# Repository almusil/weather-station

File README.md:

# weather-station

## Node
### Bulding build container
Build node building container, under project root directory: 
```
docker build --rm \
 -t weather-station/node-build-image \
 -f ./docker/Dockerfile.node \
 .
 ```

New container is needed in case you want to update libopencm3 to the latest
or bump ARM GCC version.

### Running build
Build node source, under project root directory: 
```
./scripts/run-build-node.sh
```

Open the container shell without executing the build run: 
```
./scripts/run-build-node.sh --shell
```

## Schematic and board
Schematic and board design are under HW directory

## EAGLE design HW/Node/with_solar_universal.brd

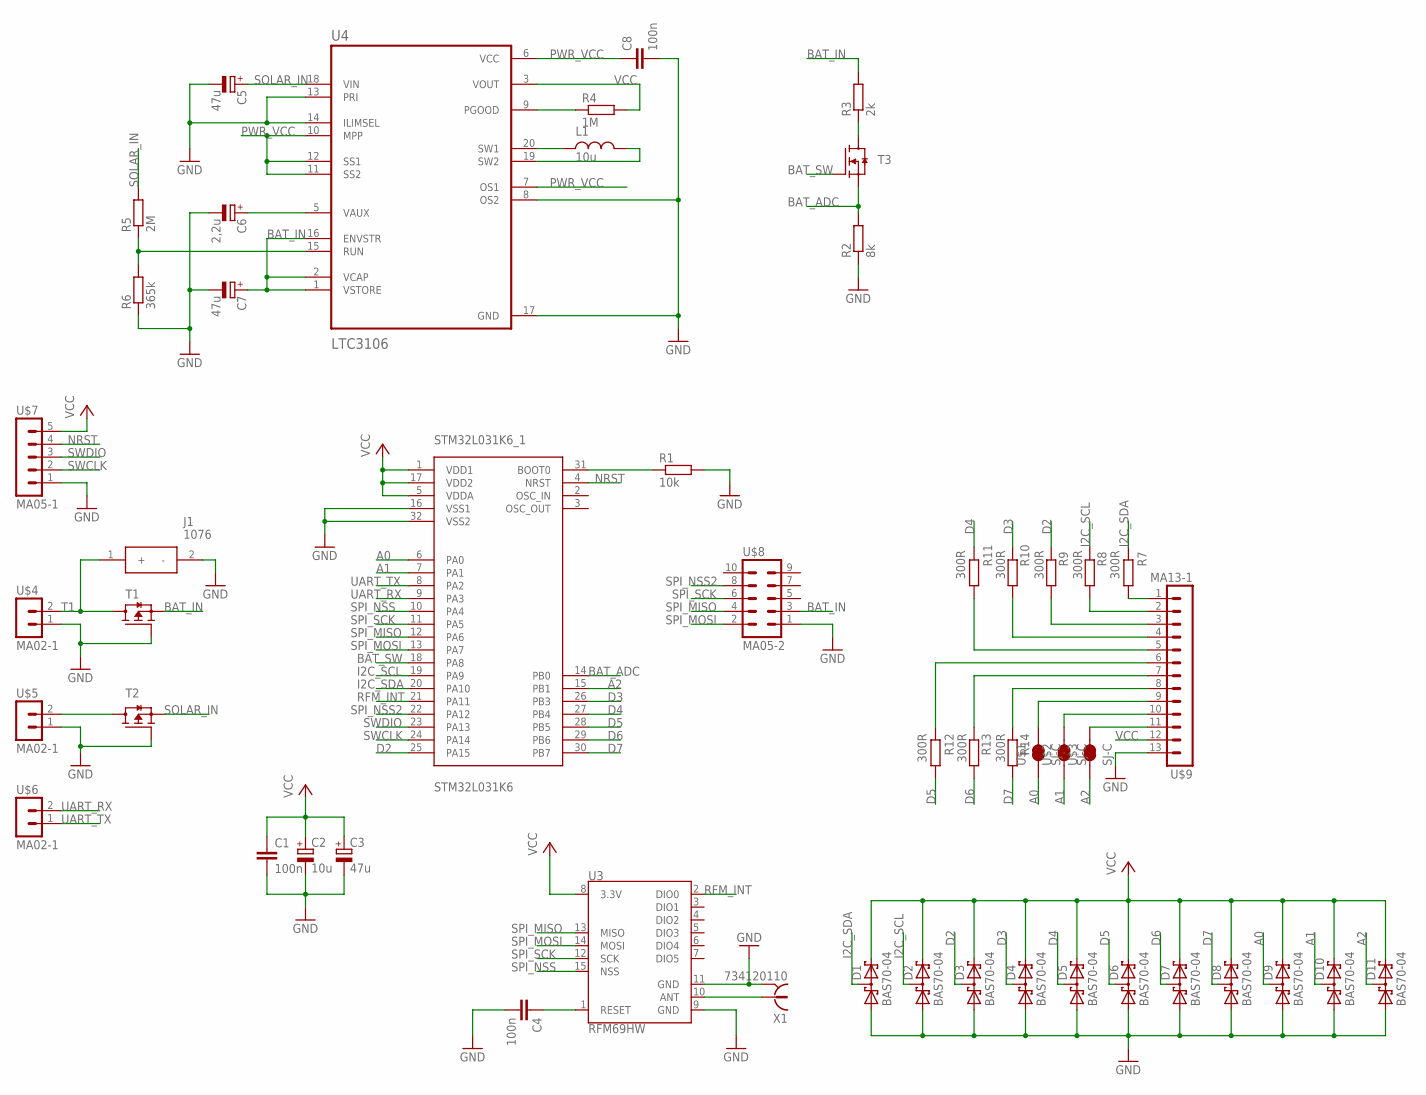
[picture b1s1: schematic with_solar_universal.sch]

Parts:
C1, C4, C8: 100n; C1206
C2: 10u; UD-4X5,8_NICHICON
C3, C5, C7: 47u; UD-4X5,8_NICHICON
C6: 2,2u; UD-4X5,8_NICHICON
D1, D2, D3, D4, D5, D6, D7, D8, D9, D10, D11: BAS70-04; SOT23
J1: 1076
L1: 10u; R1210
R1: 10k; R0805
R2: 8k; R0805
R3: 2k; R0805
R4: 1M; R0805
R5: 2M; R0805
R6: 365k; R0805
R7, R8, R9, R10, R11, R12, R13, R14: 300R; R0805
STM32L031K6_1: STM32L031K6; LQFP32-7X7
T1, T2: RTQ035P02HZG; SOT457R_PHILIPS
T3: RQ6E050AJTCR; SOT457R_PHILIPS
U3: RFM69HW; RFM69W-XXXS2
U4: LTC3106
U$1, U$2, U$3: SJ-C; R0805
U$4, U$5, U$6: MA02-1
U$7: MA05-1
U$8: MA05-2
U$9: MA13-1
X1: 734120110

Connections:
A0: D9.3 (K1A2), STM32L031K6_1.6 (PA0), U$1.1
A1: D10.3 (K1A2), STM32L031K6_1.7 (PA1), U$2.1
A2: D11.3 (K1A2), STM32L031K6_1.15 (PB1), U$3.1
BAT_ADC: R2.2, STM32L031K6_1.14 (PB0), T3.4 (S)
BAT_IN: C7.+, R3.2, T1.4 (S), U4.1 (VSTORE), U4.2 (VCAP), U4.16 (ENVSTR), U$8.3
BAT_SW: STM32L031K6_1.18 (PA8), T3.3 (G)
D2: D3.3 (K1A2), R9.2, STM32L031K6_1.25 (PA15)
D3: D4.3 (K1A2), R10.2, STM32L031K6_1.26 (PB3)
D4: D5.3 (K1A2), R11.2, STM32L031K6_1.27 (PB4)
D5: D6.3 (K1A2), R12.2, STM32L031K6_1.28 (PB5)
D6: D7.3 (K1A2), R13.2, STM32L031K6_1.29 (PB6)
D7: D8.3 (K1A2), R14.2, STM32L031K6_1.30 (PB7)
GND: C1.2, C2.-, C3.-, C4.2, C5.-, C6.-, C7.-, C8.2, D1.1 (A1), D2.1 (A1), D3.1 (A1), D4.1 (A1), D5.1 (A1), D6.1 (A1), D7.1 (A1), D8.1 (A1), D9.1 (A1), D10.1 (A1), D11.1 (A1), J1.2 (-), R1.2, R2.1, R6.1, STM32L031K6_1.16 (VSS1), STM32L031K6_1.32 (VSS2), T1.3 (G), T2.3 (G), U3.9 (GND), U3.11 (GND), U4.8 (OS2), U4.13 (PRI), U4.14 (ILIMSEL), U4.17 (GND), U$4.1 (2), U$5.1 (2), U$7.1, U$8.1, U$9.13, X1.S@1 (2), X1.S@2 (2), X1.S@3 (2)
I2C_SCL: D2.3 (K1A2), R8.2, STM32L031K6_1.19 (PA9)
I2C_SDA: D1.3 (K1A2), R7.2, STM32L031K6_1.20 (PA10)
unnamed: R1.1, STM32L031K6_1.31 (BOOT0)
unnamed: U3.10 (ANT), X1.1
unnamed: L1.1, U4.20 (SW1)
unnamed: L1.2, U4.19 (SW2)
unnamed: C6.+, U4.5 (VAUX)
unnamed: R4.1, U4.9 (PGOOD)
unnamed: R5.1, R6.2, U4.15 (RUN)
unnamed: R7.1, U$9.1
unnamed: R8.1, U$9.2
unnamed: C4.1, U3.1 (RESET)
unnamed: R9.1, U$9.3
unnamed: R10.1, U$9.4
unnamed: R11.1, U$9.5
unnamed: R12.1, U$9.6
unnamed: R13.1, U$9.7
unnamed: R14.1, U$9.8
unnamed: U$1.2, U$9.9
unnamed: U$2.2, U$9.10
unnamed: R3.1, T3.1 (D), T3.2 (D), T3.5 (D), T3.6 (D)
unnamed: U$3.2, U$9.11
NRST: STM32L031K6_1.4 (NRST), U$7.4
PWR_VCC: C8.1, U4.6 (VCC), U4.7 (OS1), U4.10 (MPP), U4.11 (SS2), U4.12 (SS1)
RFM_INT: STM32L031K6_1.21 (PA11), U3.2 (DIO0)
SOLAR_IN: C5.+, R5.2, T2.4 (S), U4.18 (VIN)
SPI_MISO: STM32L031K6_1.12 (PA6), U3.13 (MISO), U$8.4
SPI_MOSI: STM32L031K6_1.13 (PA7), U3.14 (MOSI), U$8.2
SPI_NSS: STM32L031K6_1.10 (PA4), U3.15 (NSS)
SPI_NSS2: STM32L031K6_1.22 (PA12), U$8.8
SPI_SCK: STM32L031K6_1.11 (PA5), U3.12 (SCK), U$8.6
SWCLK: STM32L031K6_1.24 (PA14), U$7.2
SWDIO: STM32L031K6_1.23 (PA13), U$7.3
T1: J1.1 (+), T1.1 (D), T1.2 (D), T1.5 (D), T1.6 (D), U$4.2 (3)
T2: T2.1 (D), T2.2 (D), T2.5 (D), T2.6 (D), U$5.2 (3)
UART_RX: STM32L031K6_1.9 (PA3), U$6.2 (3)
UART_TX: STM32L031K6_1.8 (PA2), U$6.1 (2)
VCC: C1.1, C2.+, C3.+, D1.2 (K2), D2.2 (K2), D3.2 (K2), D4.2 (K2), D5.2 (K2), D6.2 (K2), D7.2 (K2), D8.2 (K2), D9.2 (K2), D10.2 (K2), D11.2 (K2), R4.2, STM32L031K6_1.1 (VDD1), STM32L031K6_1.5 (VDDA), STM32L031K6_1.17 (VDD2), U3.8 (3.3V), U4.3 (VOUT), U$7.5, U$9.12

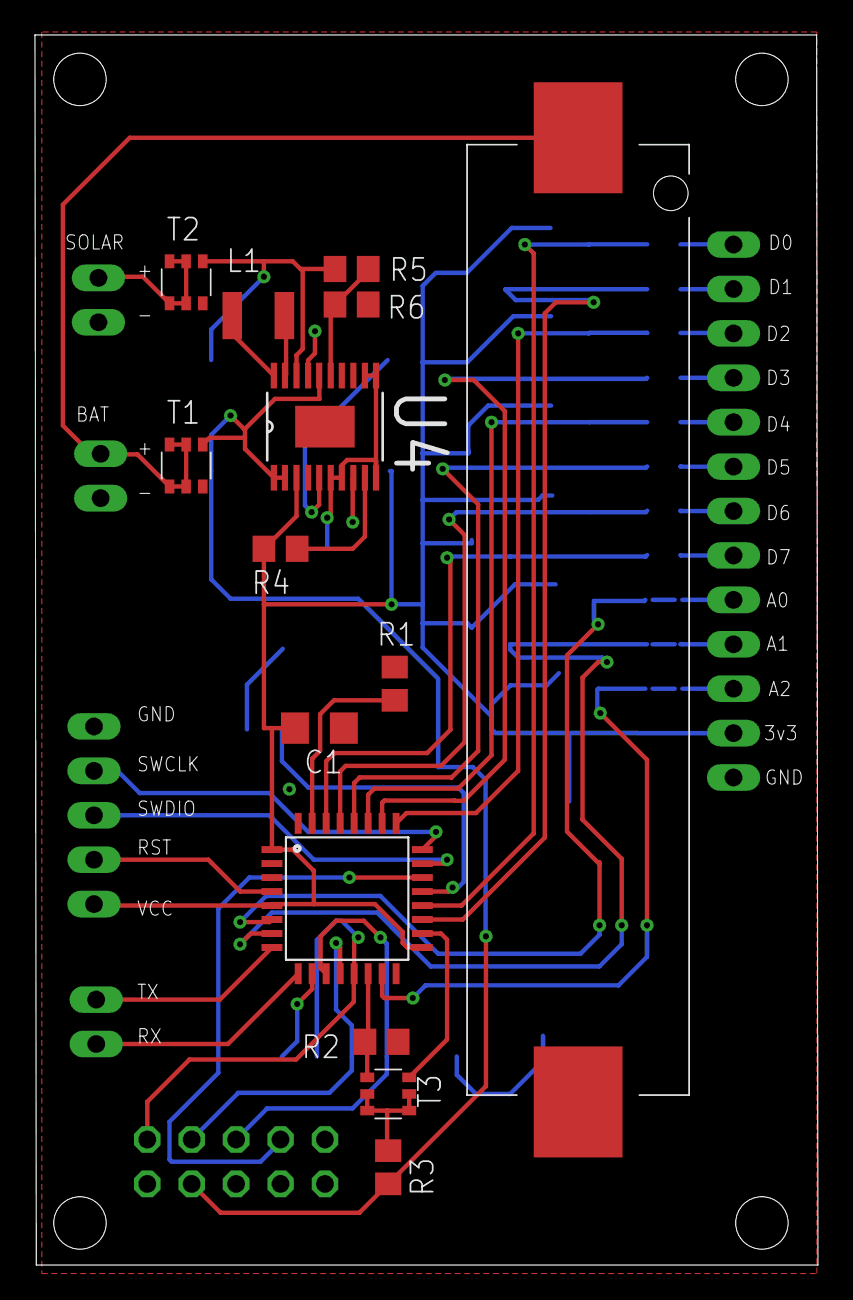
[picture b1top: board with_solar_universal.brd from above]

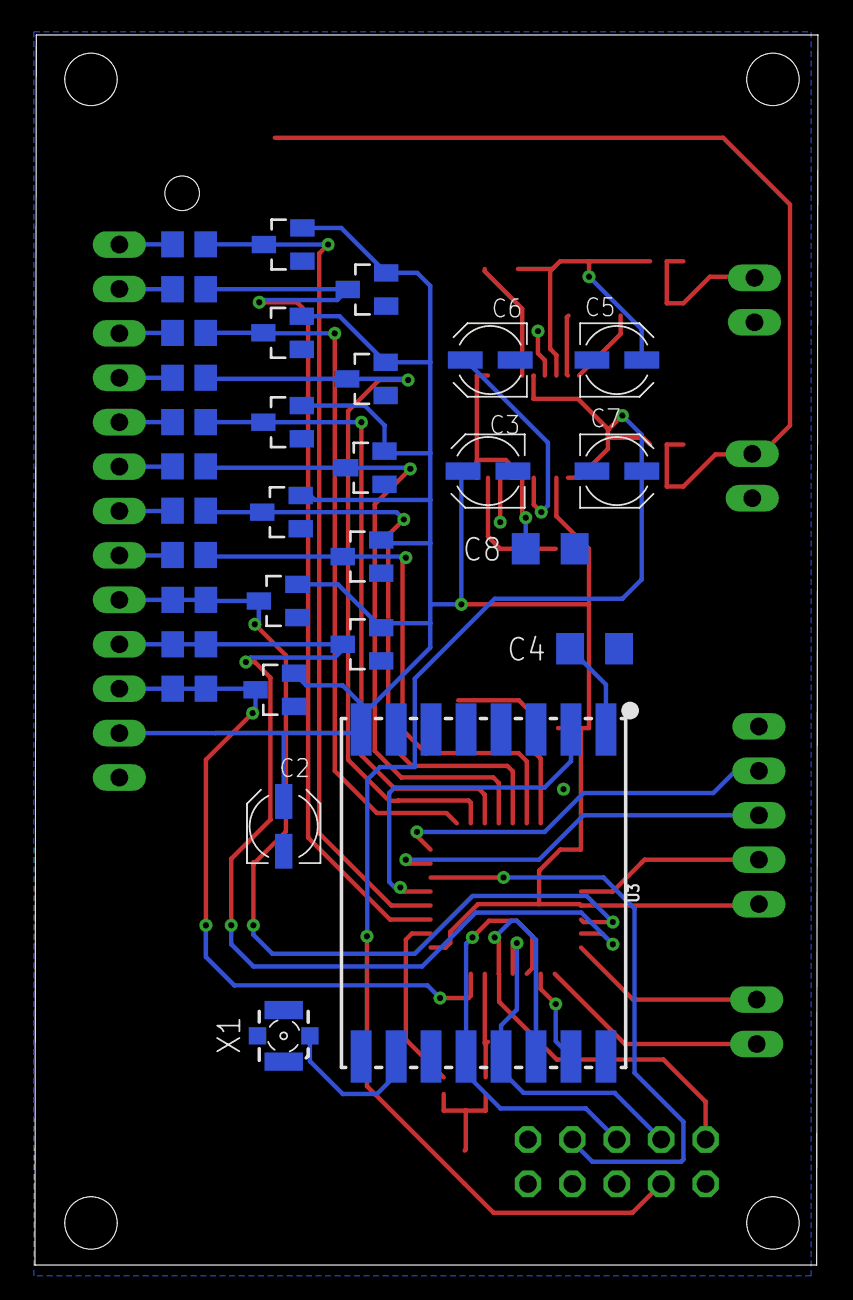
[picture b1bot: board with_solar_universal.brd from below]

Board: 2 copper layers, 44.8 x 70.3 mm, 51 parts (31 on the bottom side), 51 nets.

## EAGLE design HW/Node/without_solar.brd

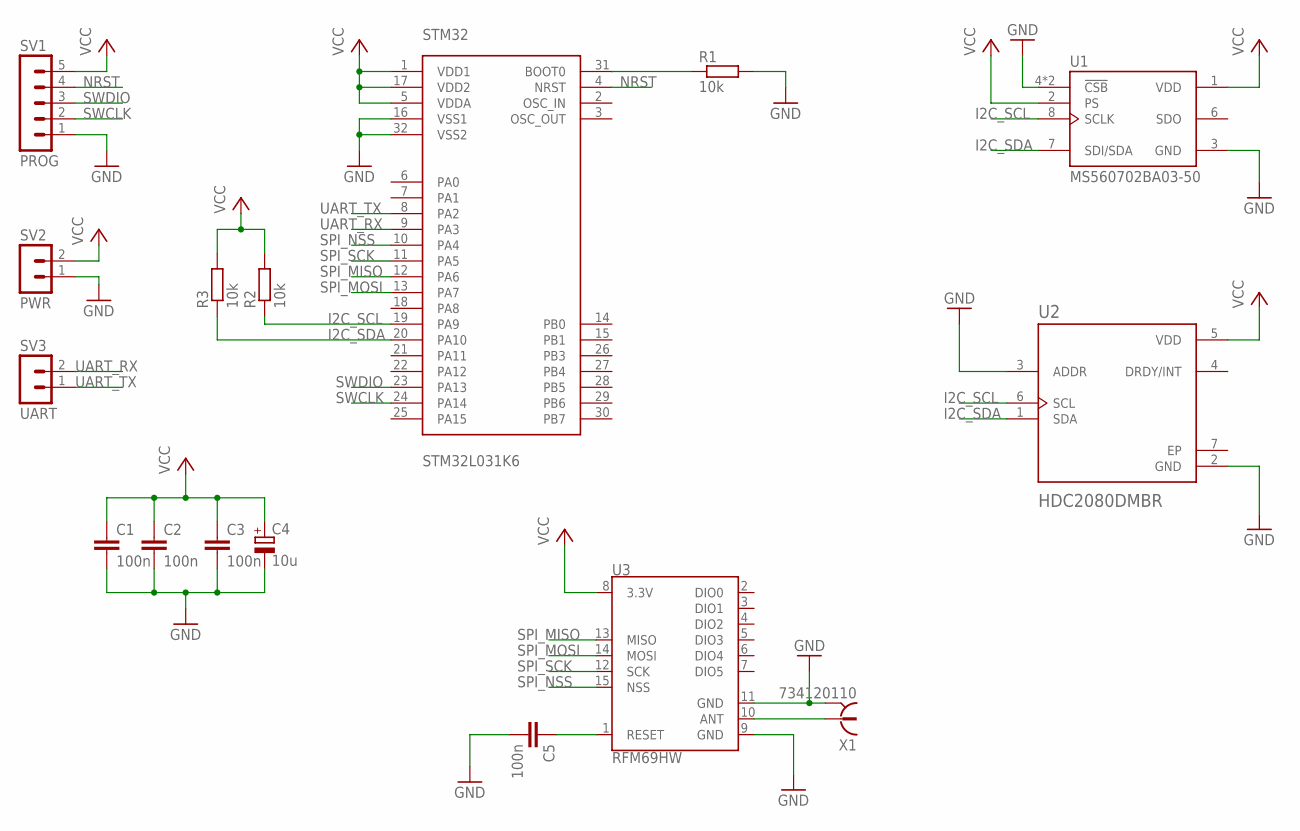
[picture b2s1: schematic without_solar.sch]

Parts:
C1, C2, C3, C5: 100n; C1206
C4: 10u; UD-4X5,8_NICHICON
R1, R2, R3: 10k; R0805
STM32: STM32L031K6; LQFP32-7X7
SV1: PROG; MA05-1
SV2: PWR; MA02-1
SV3: UART; MA02-1
U1: MS560702BA03-50; SON125P300X500X100-8N
U2: HDC2080DMBR; SON100P300X300X80-7N
U3: RFM69HW; RFM69W-XXXS2
X1: 734120110

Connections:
GND: C1.2, C2.2, C3.2, C4.-, C5.2, R1.2, STM32.16 (VSS1), STM32.32 (VSS2), SV1.1, SV2.1 (2), U1.3 (GND), U1.4 (!CSB), U1.5 (!CSB), U2.2 (GND), U2.3 (ADDR), U3.9 (GND), U3.11 (GND), X1.S@1 (2), X1.S@2 (2), X1.S@3 (2)
I2C_SCL: R2.1, STM32.19 (PA9), U1.8 (SCLK), U2.6 (SCL)
I2C_SDA: R3.1, STM32.20 (PA10), U1.7 (SDI/SDA), U2.1 (SDA)
unnamed: R1.1, STM32.31 (BOOT0)
unnamed: U3.10 (ANT), X1.1
unnamed: C5.1, U3.1 (RESET)
NRST: STM32.4 (NRST), SV1.4
RFM_INT: STM32.7 (PA1), U3.2 (DIO0)
SPI_MISO: STM32.12 (PA6), U3.13 (MISO)
SPI_MOSI: STM32.13 (PA7), U3.14 (MOSI)
SPI_NSS: STM32.10 (PA4), U3.15 (NSS)
SPI_SCK: STM32.11 (PA5), U3.12 (SCK)
SWCLK: STM32.24 (PA14), SV1.2
SWDIO: STM32.23 (PA13), SV1.3
UART_RX: STM32.9 (PA3), SV3.2 (3)
UART_TX: STM32.8 (PA2), SV3.1 (2)
VCC: C1.1, C2.1, C3.1, C4.+, R2.2, R3.2, STM32.1 (VDD1), STM32.5 (VDDA), STM32.17 (VDD2), SV1.5, SV2.2 (3), U1.1 (VDD), U1.2 (PS), U2.5 (VDD), U3.8 (3.3V)

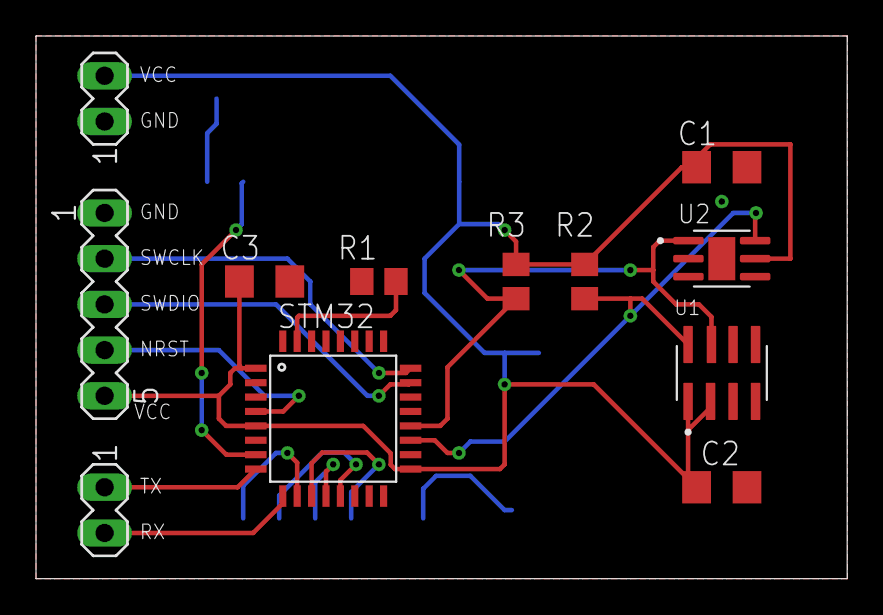
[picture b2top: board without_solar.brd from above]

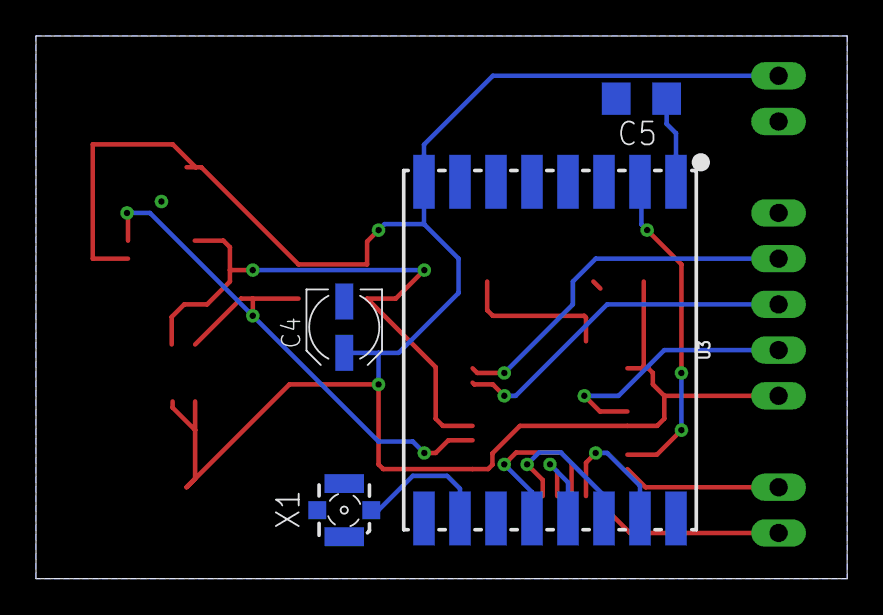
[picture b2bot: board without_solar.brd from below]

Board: 2 copper layers, 45.1 x 30.1 mm, 16 parts (4 on the bottom side), 17 nets.

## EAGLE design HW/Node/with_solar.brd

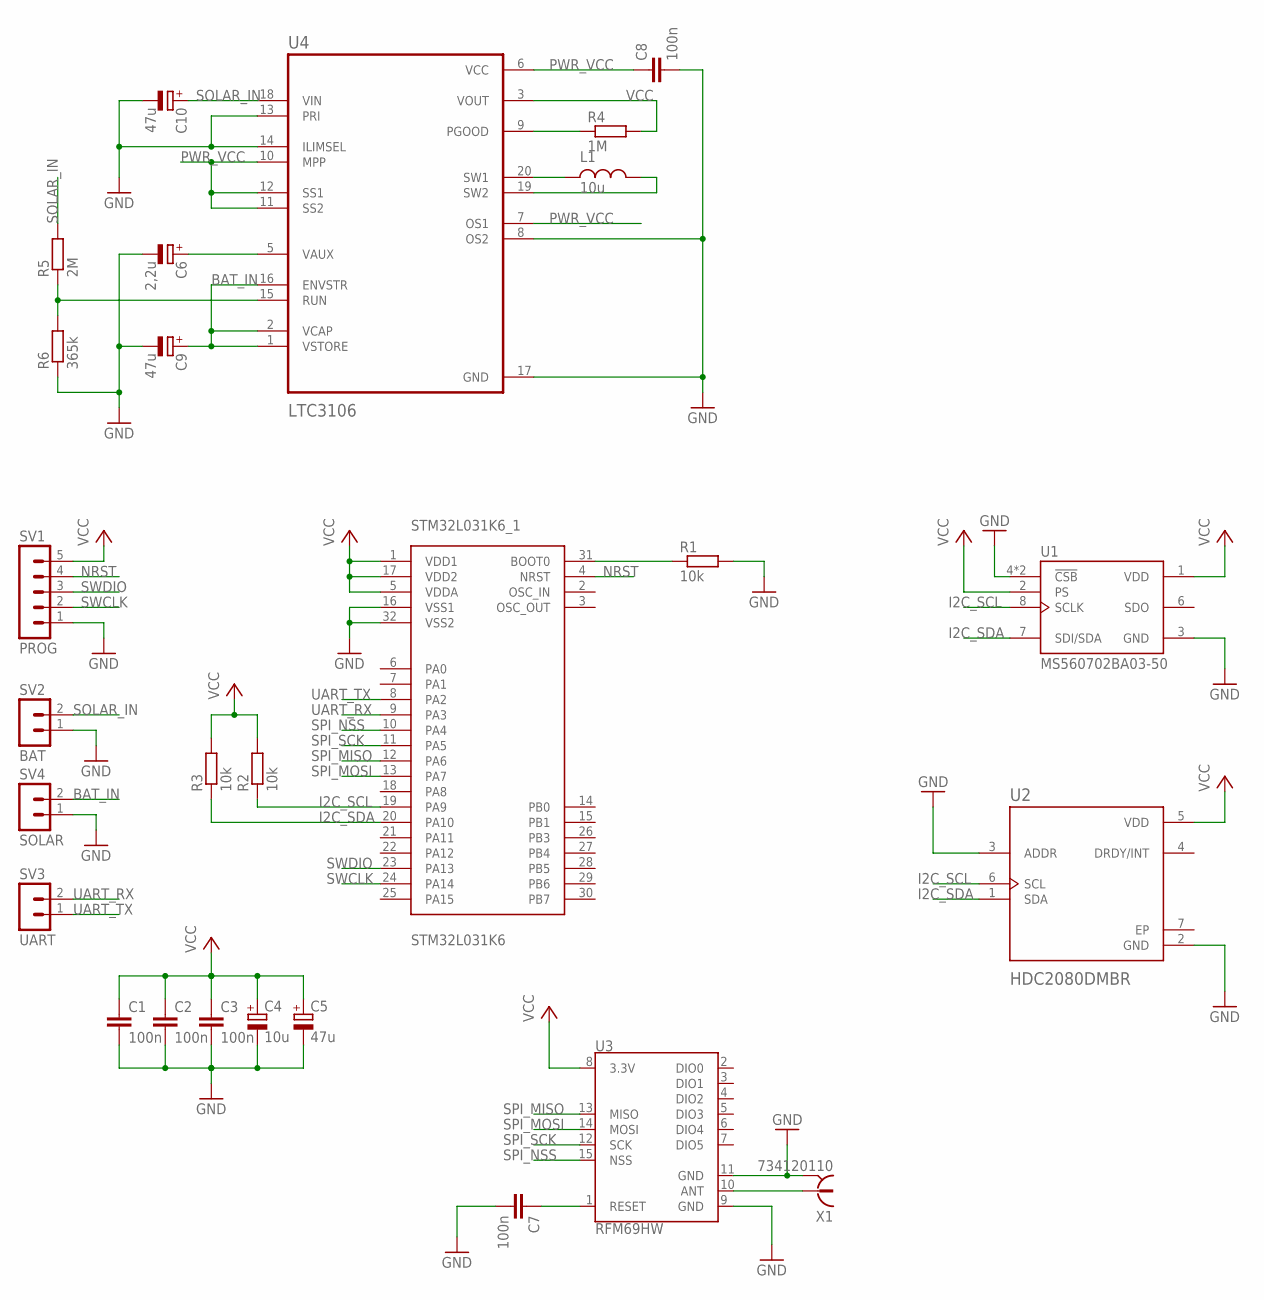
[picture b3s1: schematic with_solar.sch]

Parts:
C1, C2, C3, C7, C8: 100n; C1206
C4: 10u; UD-4X5,8_NICHICON
C5, C9, C10: 47u; UD-4X5,8_NICHICON
C6: 2,2u; UD-4X5,8_NICHICON
L1: 10u; R1210
R1, R2, R3: 10k; R0805
R4: 1M; R0805
R5: 2M; R0805
R6: 365k; R0805
STM32L031K6_1: STM32L031K6; LQFP32-7X7
SV1: PROG; MA05-1
SV2: BAT; MA02-1
SV3: UART; MA02-1
SV4: SOLAR; MA02-1
U1: MS560702BA03-50; SON125P300X500X100-8N
U2: HDC2080DMBR; SON100P300X300X80-7N
U3: RFM69HW; RFM69W-XXXS2
U4: LTC3106
X1: 734120110

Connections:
BAT_IN: C9.+, SV4.2 (3), U4.1 (VSTORE), U4.2 (VCAP), U4.16 (ENVSTR)
GND: C1.2, C2.2, C3.2, C4.-, C5.-, C6.-, C7.2, C8.2, C9.-, C10.-, R1.2, R6.1, STM32L031K6_1.16 (VSS1), STM32L031K6_1.32 (VSS2), SV1.1, SV2.1 (2), SV4.1 (2), U1.3 (GND), U1.4 (!CSB), U1.5 (!CSB), U2.2 (GND), U2.3 (ADDR), U3.9 (GND), U3.11 (GND), U4.8 (OS2), U4.13 (PRI), U4.14 (ILIMSEL), U4.17 (GND), X1.S@1 (2), X1.S@2 (2), X1.S@3 (2)
I2C_SCL: R2.1, STM32L031K6_1.19 (PA9), U1.8 (SCLK), U2.6 (SCL)
I2C_SDA: R3.1, STM32L031K6_1.20 (PA10), U1.7 (SDI/SDA), U2.1 (SDA)
unnamed: R1.1, STM32L031K6_1.31 (BOOT0)
unnamed: U3.10 (ANT), X1.1
unnamed: L1.1, U4.20 (SW1)
unnamed: L1.2, U4.19 (SW2)
unnamed: C6.+, U4.5 (VAUX)
unnamed: R4.1, U4.9 (PGOOD)
unnamed: R5.1, R6.2, U4.15 (RUN)
unnamed: C7.1, U3.1 (RESET)
NRST: STM32L031K6_1.4 (NRST), SV1.4
PWR_VCC: C8.1, U4.6 (VCC), U4.7 (OS1), U4.10 (MPP), U4.11 (SS2), U4.12 (SS1)
SOLAR_IN: C10.+, R5.2, SV2.2 (3), U4.18 (VIN)
SPI_MISO: STM32L031K6_1.12 (PA6), U3.13 (MISO)
SPI_MOSI: STM32L031K6_1.13 (PA7), U3.14 (MOSI)
SPI_NSS: STM32L031K6_1.10 (PA4), U3.15 (NSS)
SPI_SCK: STM32L031K6_1.11 (PA5), U3.12 (SCK)
SWCLK: STM32L031K6_1.24 (PA14), SV1.2
SWDIO: STM32L031K6_1.23 (PA13), SV1.3
UART_RX: STM32L031K6_1.9 (PA3), SV3.2 (3)
UART_TX: STM32L031K6_1.8 (PA2), SV3.1 (2)
VCC: C1.1, C2.1, C3.1, C4.+, C5.+, R2.2, R3.2, R4.2, STM32L031K6_1.1 (VDD1), STM32L031K6_1.5 (VDDA), STM32L031K6_1.17 (VDD2), SV1.5, U1.1 (VDD), U1.2 (PS), U2.5 (VDD), U3.8 (3.3V), U4.3 (VOUT)

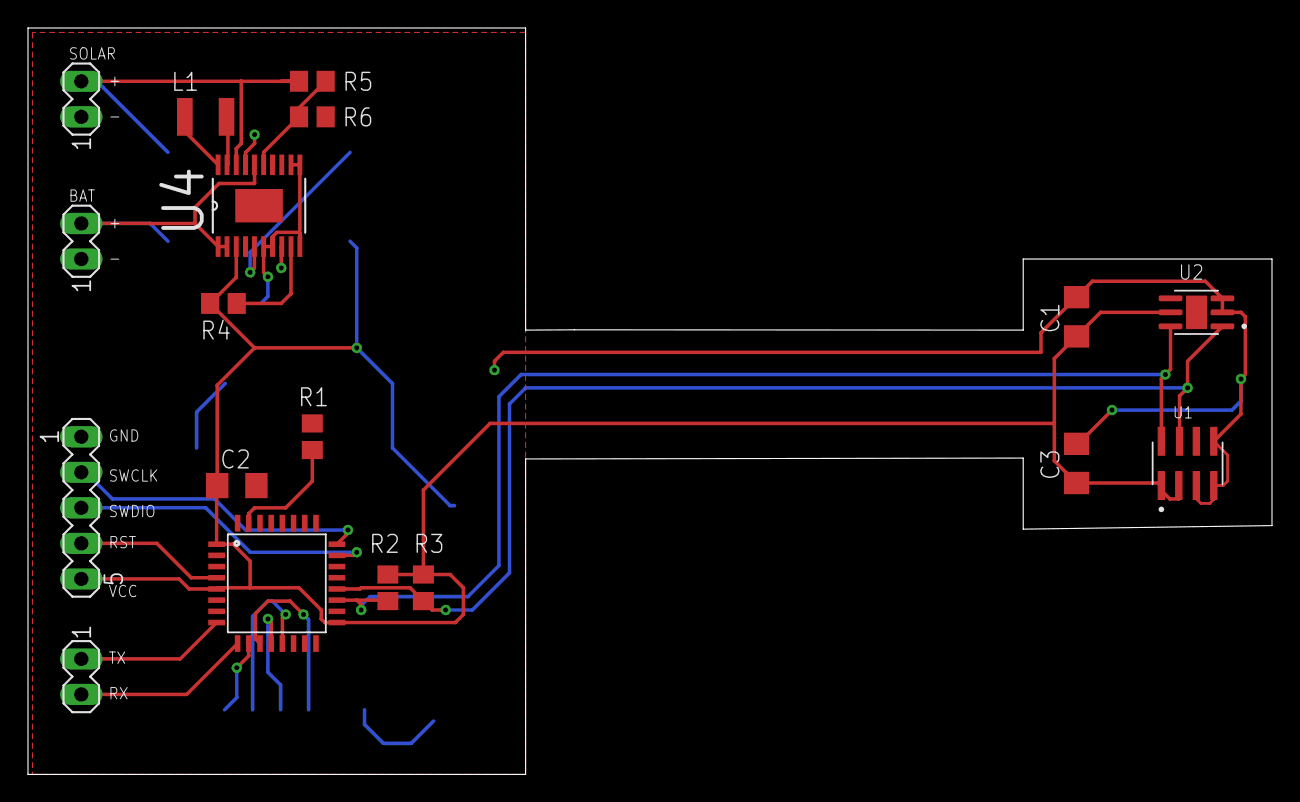
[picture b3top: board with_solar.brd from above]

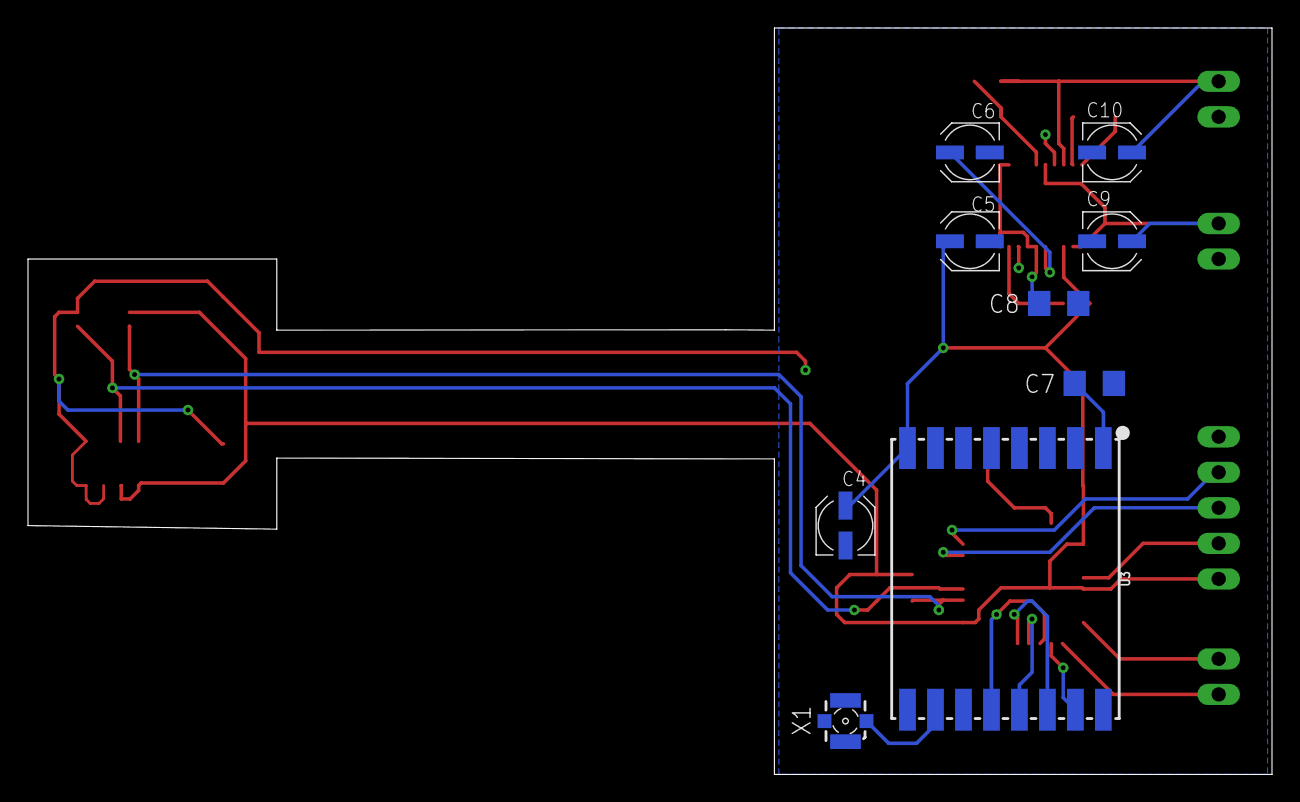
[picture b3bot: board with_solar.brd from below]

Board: 2 copper layers, 88.9 x 53.3 mm, 27 parts (9 on the bottom side), 24 nets.

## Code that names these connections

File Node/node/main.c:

#include <libopencm3/stm32/rcc.h>
#include <libopencm3/stm32/gpio.h>
#include <libopencm3/stm32/pwr.h>

#include <periph/sys_tick.h>
#include <periph/rtc.h>
#include <periph/low_power.h>
#include <periph/spi.h>
#include <periph/usart.h>
#include <periph/adc.h>
#include <periph/gpio.h>
#include <periph/i2c.h>
#include <config.h>
#include <rfm69.h>
#include <bme280.h>

static struct config conf = {
        .sleep_time = 10,
        .dio_direction = 0x00,
        .dio_value = 0x00,
        .analog = BAT_CHANNEL
};

static void clock_setup(void);

static void gpio_setup(void);

static void setup(void);

static void deep_sleep(void);

static void before_sleep(void);

static void after_wakeup(void);

static bool packet_received(void);

static void update_config(void);

static void send_measured_data(void);

static void clock_setup() {
    //Setup clock to internal 16MHz
    rcc_osc_on(RCC_HSI16);
    rcc_wait_for_osc_ready(RCC_HSI16);

    //Enable SysClock to 16Mhz
    rcc_set_sysclk_source(RCC_HSI16);

    rcc_ahb_frequency = 16e6;
    rcc_apb1_frequency = 16e6;
    rcc_apb2_frequency = 16e6;

    rcc_periph_clock_enable(RCC_GPIOA);
    rcc_periph_clock_enable(RCC_GPIOB);
    rcc_periph_clock_enable(SPI_CLOCK);
    rcc_periph_clock_enable(RCC_PWR);
    rcc_periph_clock_enable(USART_CLOCK);
    rcc_periph_clock_enable(ADC_CLOCK);
    rcc_periph_clock_enable(I2C_CLOCK);
}


static void gpio_setup() {
    /*  SPI GPIO setup */
    gpio_mode_setup(SPI_PORT, GPIO_MODE_AF, GPIO_PUPD_NONE, SPI_SCK | SPI_MISO | SPI_MOSI);
    gpio_set_output_options(SPI_PORT, GPIO_OTYPE_PP, GPIO_OSPEED_VERYHIGH, SPI_SCK | SPI_MISO | SPI_MOSI);
    gpio_set_af(SPI_PORT, GPIO_AF0, SPI_SCK | SPI_MISO | SPI_MOSI);

    gpio_clear(RFM69_PORT, RFM69_NSS);
    gpio_mode_setup(RFM69_PORT, GPIO_MODE_OUTPUT, GPIO_PUPD_NONE, RFM69_NSS);
    gpio_set(RFM69_PORT, RFM69_NSS);

    /* I2C GPIO setup */
    gpio_mode_setup(I2C_PORT, GPIO_MODE_AF, GPIO_PUPD_NONE, I2C_SDA | I2C_SCL);
    /* I2C pins have to open-drain */
    gpio_set_output_options(I2C_PORT, GPIO_OTYPE_OD, GPIO_OSPEED_LOW, I2C_SDA | I2C_SCL);
    gpio_set_af(I2C_PORT, GPIO_AF1, I2C_SDA | I2C_SCL);

    /* RFM69 interrupt setup */
    gpio_mode_setup(RFM69_PORT, GPIO_MODE_INPUT, GPIO_PUPD_PULLDOWN, RFM69_INT);

    /* USART GPIO setup */
    gpio_mode_setup(USART_PORT, GPIO_MODE_AF, GPIO_PUPD_NONE, USART_TX | USART_RX);
    gpio_set_af(USART_PORT, GPIO_AF4, USART_TX | USART_RX);

    /* ADC GPIO setup */
    gpio_mode_setup(ADC_PORT1, GPIO_MODE_ANALOG, GPIO_PUPD_NONE, A0 | A1);
    gpio_mode_setup(ADC_PORT2, GPIO_MODE_ANALOG, GPIO_PUPD_NONE, BAT_ADC | A2);

    /* Battery switch */
    gpio_mode_setup(SW_PORT, GPIO_MODE_OUTPUT, GPIO_PUPD_NONE, SW_PIN);
    gpio_clear(SW_PORT, SW_PIN);
}

static void setup() {
    clock_setup();
    gpio_setup();
    sys_tick_setup();
    spi_setup();
    rtc_setup();
    usart_setup(USART_SPEED);
    rfm69_setup();
    adc_setup();
    i2c_setup();
    bme_setup();
    gpio_dio_setup(conf.dio_direction, conf.dio_value);
}

static void deep_sleep() {
    before_sleep();
    enter_stop_mode();
    after_wakeup();
}

static void before_sleep() {
    printf("Going to sleep!\n");
    sys_tick_disable();
    usart_interrupt_disable();
    rtc_wakeup_setup(conf.sleep_time);
    rfm69_sleep();
    spi_lib_disable();
    i2c_disable();
}

static void after_wakeup() {
    rtc_disable();
    sys_tick_enable();
    usart_interrupt_enable();
    spi_lib_enable();
    rfm69_wakeup();
    i2c_enable();
    printf("Back from sleep!\n");
}

static bool packet_received() {
    uint64_t now = get_millis();
    bool done = rfm69_receive_done();
    while (!done && get_millis() - now < CONFIG_TIMEOUT) {
        done = rfm69_receive_done();
    }
    printf("Received %d!\n", done);
    return done;
}

static void update_config() {
    struct rfm69_packet packet = {0};
    rfm69_get_data(&packet);
    if (packet.sender_id == GATEWAY_ADDR &&
        packet.target_id == NODE_ADDR &&
        packet.data_len == CONFIG_LENGTH + 1 &&
        packet.data_buffer[0] == PACKET_CONFIG) {
        // Update conf
        conf.sleep_time = (packet.data_buffer[2] << 8) | packet.data_buffer[1];
        conf.dio_direction = packet.data_buffer[3];
        conf.dio_value = packet.data_buffer[4];
        conf.analog = (packet.data_buffer[5] & 0x07) | BAT_CHANNEL;

        // Call gpio_setup
        gpio_dio_setup(conf.dio_direction, conf.dio_value);
        printf("Got new config!\n");
    }
}

static void send_measured_data() {
    printf("Sending measured data!\n");
    union packet_t packet = {0};
    uint16_t adc[4] = {0};

    bme_start_measurement();
    gpio_set(SW_PORT, SW_PIN);
    adc_convert(conf.analog, adc, 4);
    gpio_clear(SW_PORT, SW_PIN);

    if (conf.analog & A2_CHANNEL) {
        // Swap A2 and BAT adc data
        uint16_t tmp = adc[2];
        adc[2] = adc[3];
        adc[3] = tmp;
    }

    packet.data.packet_type = PACKET_DATA;
    packet.data.gpio_value = read_gpio_value();

    for (uint8_t i = 0; i < 4; i++) {
        packet.data.adc_value[i] = adc[i];
    }

    while (!bme_measure_done());

    packet.data.temperature = bme_get_temp();
    packet.data.pressure = bme_get_pressure();

    packet.data.humidity = bme_get_humidity();


    for (uint8_t i = 0; i < ACK_RETRY_COUNT; i++) {
        rfm69_send(GATEWAY_ADDR, &packet.bytes, sizeof(union packet_t), true);
        uint64_t now = get_millis();
        bool done = rfm69_ack_received(GATEWAY_ADDR);
        while (!done && get_millis() - now < ACK_TIMEOUT) {
            done = rfm69_ack_received(GATEWAY_ADDR);
        }
        if (done) {
            printf("Got ACK!\n");
            break;
        }
    }
}

int main(void) {
    setup();
    delay(1000);
    while (1) {
        uint8_t buffer = {PACKET_CONFIG};
        rfm69_send(GATEWAY_ADDR, &buffer, 1, false);
        bool new_packet = packet_received();
        if (new_packet) {
            update_config();
        }
        send_measured_data();
        deep_sleep();
    }
}

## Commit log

2019-08-31 Node: Initial node commit
2019-08-31 HW: Add Node schematic and board design
2019-09-21 Node, rfm69: Fix SPI communication
2019-09-21 Node, rfm69: Add rfm69 register defines
    Use rfm69 register defines from [1]
    [1] https://github.com/LowPowerLab/RFM69
2019-09-21 Node, rfm69: Add interrupt routine for rfm69 interrupts
2019-09-21 Node, SPI: Add method to enable/disable SPI
    Use enable after wakeup and disable before sleep to save most of the
    during low power.
2019-09-21 Node: Make function logical order more readable
2019-09-22 Node, rfm69: Add setup function and all necessary functions
2019-09-26 Node, rfm69: Add current state to track our current settings
2019-10-04 Node, rfm69: Add send and receive functionality
    Add functions required to send and receive payload
    that is compatible with LowPowerLab Arduino library[1].
    [1] https://github.com/LowPowerLab/RFM69
2019-10-11 HW: Update node schematic and board
2019-10-20 HW: Update node schematic and board
    - Use different input protection.
    - Add current limiting resistor.
    - Add AAA battery holder.
2019-10-28 Node, rfm69: Fix interrupt pin and handler
    Interrupt for rfm69 moved to pin GPIOA11. We need to shift the EXTI
    and NVIC accordingly.
2019-10-28 Node: Add support for ADC defined according to schematic
2019-11-28 Node: Prepare for reproducible container builds
    - Rename project to node (more relevant)
    - Expose libopencm3 dir env variable
2019-11-29 Node: Add support for container builds
    From now on the code build can be reproducible on any machine
    using the container.
    Container can be built by running:
    docker build --rm \
    -t weather-station/node-build-image \
    -f ./docker/Dockerfile.node \
2019-11-29 Node: Remove dependency on libopencm3 as module
2020-01-02 Gateway: Add mosquitto and home assistant container
    Add mosquitto and home-assistant container and
    connect them together in the same namespace.
    Configure mosqiutto to listen only on localhost
    preventing anything from outside to be able to connect
    except apps running in the same "pod".
2020-01-02 Node: Remove I2C files
2020-01-03 Gateway: Add basic proxy
    Proxy communicates with RFM69 and Home Assistant through
    the MQTT.
2020-01-03 Node: Add main loop with config
2020-01-03 Node: Update container image
2020-01-03 Gateway: Move proxy struct into its own module
2020-01-03 Gateway: Add better error handling and error progataion
2020-01-03 Gateway: Add logging into file
2020-01-03 Gateway: Update order of functions and struct
2020-01-03 Gateway: Add value expression into config
2020-01-03 Gateway: Update gateway container
2020-01-26 Node: Some minor fixes
    - Create proper .gdbinit file to upload program with Black
    Magic Probe
    - Fix UART RX pin assigment
    - Add sleep before program starts in order to make it
    easier for GDB to break program before sleep.
    - Swap BAT and A2 values before sending them
2020-01-26 Gateway: Update pin management
    Update Linux Embedded Hal pin management according to
    lastest changes.
2020-01-26 Gateway: Inlcude Cargo.lock file
2020-02-20 Gateway: Update Dockerfile
2020-02-20 Gateway: Wait for a proper rfm interrupt
    To prevent 100% CPU load add loop that will wait
    for the proper receive interrupt.
2020-02-20 Node: Fix reading of battery voltage
2020-02-20 Gateway: Update async-std dependency
2020-02-20 Gateway: Update battery template to compute exact voltage
2020-03-16 Node: Add I2C periph library
2020-03-18 Node: Add BME280 for basic weather measurements
2020-03-18 Gateway: Add reporting of weather sensor
2020-03-20 Node, Gateway: Improve data serialization/deserialization
2020-03-22 Gateway: Add out of bound check for received packet
2020-03-22 Node: Update prescalers for RTC
2020-03-22 Gateway: Add vutbr server
2020-03-25 Gateway: Update rfm69 dependency and error
2020-04-02 Gateway: Update dockerfile to cache dependency builds
2020-04-02 Gateway: Update running script
    - Include the env variable for VUT MQTT uri
    - Use older home-assistant image, latest has regression
2022-06-06 Bump crossbeam-deque from 0.7.3 to 0.7.4 in /Gateway/proxy
    Bumps [crossbeam-deque](https://github.com/crossbeam-rs/crossbeam) from 0.7.3 to 0.7.4.
    - [Release notes](https://github.com/crossbeam-rs/crossbeam/releases)
    - [Changelog](https://github.com/crossbeam-rs/crossbeam/blob/master/CHANGELOG.md)
    - [Commits](https://github.com/crossbeam-rs/crossbeam/compare/crossbeam-0.7.3...crossbeam-deque-0.7.4)
    ---
    updated-dependencies:
2022-06-06 Bump linked-hash-map from 0.5.2 to 0.5.4 in /Gateway/proxy
    Bumps [linked-hash-map](https://github.com/contain-rs/linked-hash-map) from 0.5.2 to 0.5.4.
    - [Release notes](https://github.com/contain-rs/linked-hash-map/releases)
    - [Commits](https://github.com/contain-rs/linked-hash-map/commits)
    ---
    updated-dependencies:
    - dependency-name: linked-hash-map
2022-06-06 Bump crossbeam-channel from 0.4.2 to 0.4.4 in /Gateway/proxy
    Bumps [crossbeam-channel](https://github.com/crossbeam-rs/crossbeam) from 0.4.2 to 0.4.4.
    - [Release notes](https://github.com/crossbeam-rs/crossbeam/releases)
    - [Changelog](https://github.com/crossbeam-rs/crossbeam/blob/master/CHANGELOG.md)
    - [Commits](https://github.com/crossbeam-rs/crossbeam/compare/v0.4.2...crossbeam-channel-0.4.4)
    ---
    updated-dependencies:

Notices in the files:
parts and their libraries:
SparkFun-RF: Licensing: Creative Commons ShareAlike 4.0 International - https://creativecommons.org/licenses/by-sa/4.0
